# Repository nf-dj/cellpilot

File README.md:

# CellPilot

A controller to pilot UAV/drones via 3G/4G cellular connection.

WARNING: this version of CellPilot will soon be replaced by a new controller using TinyCom instead of Raspberry Pi (http://github.com/nfco/tinycom).

## Pictures

A view of the PCB, a Raspberry Pi "hat":

Inside a 3d-printed prototype box:

CellPilot installed on a DIY drone:

We still rely on an external controller for stabilization.
But a 10DOF sensor module can be installed on the CellPilot board and we can later try to do the stabilization directly on the STM32 processor of the board. (a prototype firmware to do this is already in the repository)

## Video

CellPilot test flight (64Kbps, 10fps):

(the strange colors in the video are due to the PiNoir camera, we will make a new video with a regular Pi camera and some vibration dampening)

## Ordering

A 3d-printed plastic case can be ordered here:
https://www.shapeways.com/shops/netforce

## Contact

Send email to dj@netforce.com.

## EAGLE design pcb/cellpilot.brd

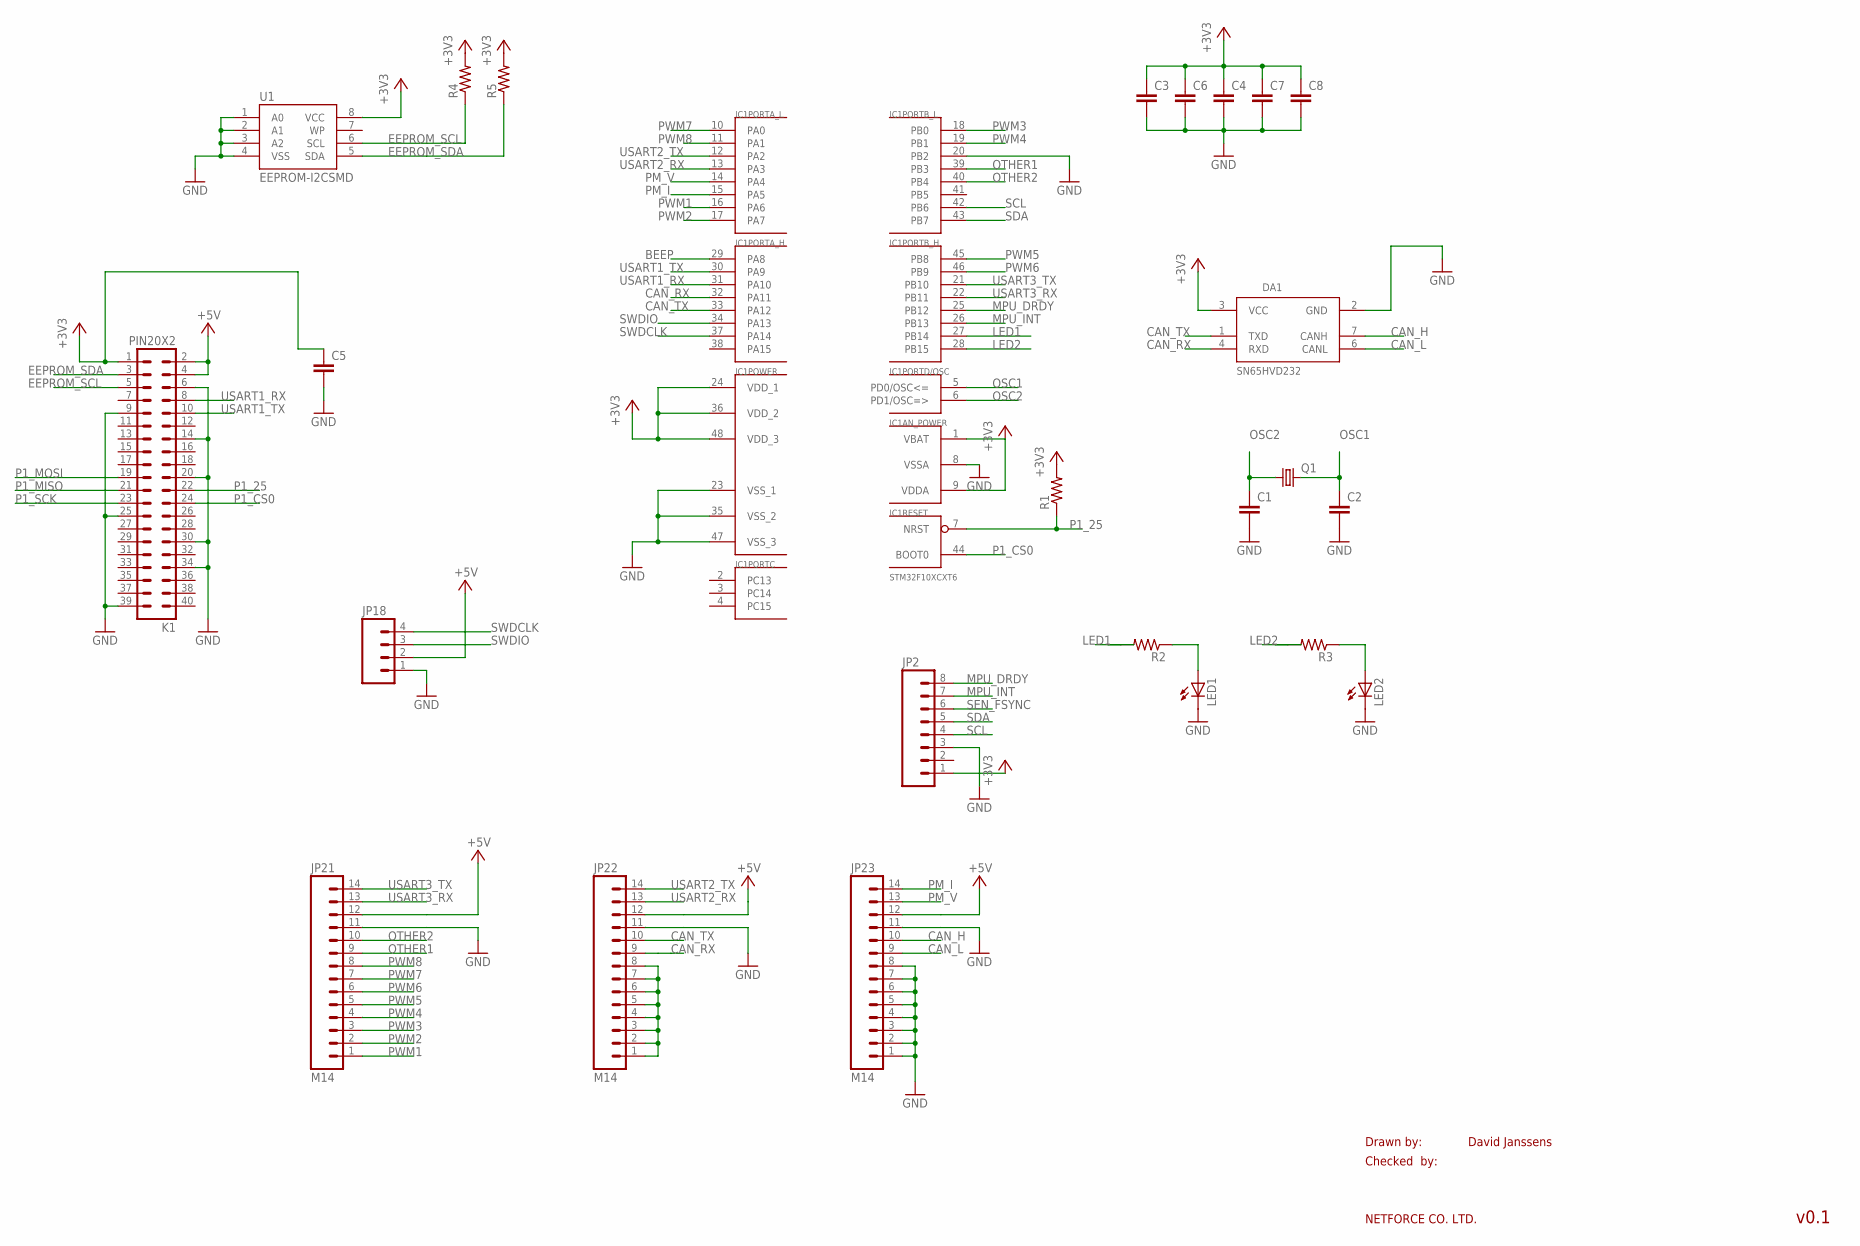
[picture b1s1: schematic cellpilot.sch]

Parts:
C1, C2, C3, C4, C5, C6, C7, C8: CAP0805; 0805
DA1: SN65HVD232; SO08
IC1: STM32F10XCXT6; TQFP48
JP2: M08; 1X08_ROUND
JP18: M04PTH; 1X04
JP21, JP22, JP23: M14; 1X14
K1: PIN20X2; PIN_20X2
LED1, LED2: LED3MM
Q1: CRYSTALHC49S; HC49/S
R1, R2, R3, R4, R5: RESISTOR0805-RES; 0805
U1: EEPROM-I2CSMD; SO08

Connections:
+3V3: C3.1, C4.1, C5.1, C6.1, C7.1, C8.1, DA1.3 (VCC), IC1.1 (VBAT), IC1.9 (VDDA), IC1.24 (VDD_1), IC1.36 (VDD_2), IC1.48 (VDD_3), JP2.1, K1.1, R1.2, R4.2, R5.2, U1.8 (VCC)
+5V: JP18.2, JP21.12, JP22.12, JP23.12, K1.2, K1.4
BEEP: IC1.29 (PA8)
CAN_H: DA1.7 (CANH), JP23.10
CAN_L: DA1.6 (CANL), JP23.9
CAN_RX: DA1.4 (RXD), IC1.32 (PA11), JP22.9
CAN_TX: DA1.1 (TXD), IC1.33 (PA12), JP22.10
EEPROM_SCL: K1.5, R4.1, U1.6 (SCL)
EEPROM_SDA: K1.3, R5.1, U1.5 (SDA)
GND: C1.2, C2.2, C3.2, C4.2, C5.2, C6.2, C7.2, C8.2, DA1.2 (GND), IC1.8 (VSSA), IC1.20 (PB2), IC1.23 (VSS_1), IC1.35 (VSS_2), IC1.47 (VSS_3), JP2.3, JP18.1, JP21.11, JP22.11, JP23.1, JP23.2, JP23.3, JP23.4, JP23.5, JP23.6, JP23.7, JP23.8, JP23.11, K1.6, K1.9, K1.14, K1.20, K1.25, K1.30, K1.34, K1.39, LED1.K (C), LED2.K (C), U1.1 (A0), U1.2 (A1), U1.3 (A2), U1.4 (VSS)
LED1: IC1.27 (PB14), R2.2
LED2: IC1.28 (PB15), R3.2
MPU_DRDY: IC1.25 (PB12), JP2.8
MPU_INT: IC1.26 (PB13), JP2.7
unnamed: LED1.A, R2.1
unnamed: JP22.1, JP22.2, JP22.3, JP22.4, JP22.5, JP22.6, JP22.7, JP22.8
unnamed: LED2.A, R3.1
OSC1: C2.1, IC1.5 (PD0/OSC<=), Q1.2
OSC2: C1.1, IC1.6 (PD1/OSC=>), Q1.1
OTHER1: IC1.39 (PB3), JP21.9
OTHER2: IC1.40 (PB4), JP21.10
P1_25: IC1.7 (NRST), K1.22, R1.1
P1_CS0: IC1.44 (BOOT0), K1.24
P1_MISO: K1.21
P1_MOSI: K1.19
P1_SCK: K1.23
PM_I: IC1.15 (PA5), JP23.14
PM_V: IC1.14 (PA4), JP23.13
PWM1: IC1.16 (PA6), JP21.1
PWM2: IC1.17 (PA7), JP21.2
PWM3: IC1.18 (PB0), JP21.3
PWM4: IC1.19 (PB1), JP21.4
PWM5: IC1.45 (PB8), JP21.5
PWM6: IC1.46 (PB9), JP21.6
PWM7: IC1.10 (PA0), JP21.7
PWM8: IC1.11 (PA1), JP21.8
SCL: IC1.42 (PB6), JP2.4
SDA: IC1.43 (PB7), JP2.5
SEN_FSYNC: JP2.6
SWDCLK: IC1.37 (PA14), JP18.4
SWDIO: IC1.34 (PA13), JP18.3
USART1_RX: IC1.31 (PA10), K1.8
USART1_TX: IC1.30 (PA9), K1.10
USART2_RX: IC1.13 (PA3), JP22.13
USART2_TX: IC1.12 (PA2), JP22.14
USART3_RX: IC1.22 (PB11), JP21.13
USART3_TX: IC1.21 (PB10), JP21.14

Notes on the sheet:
Drawn by:
Checked by:
NETFORCE CO. LTD.
David Janssens
v0.1

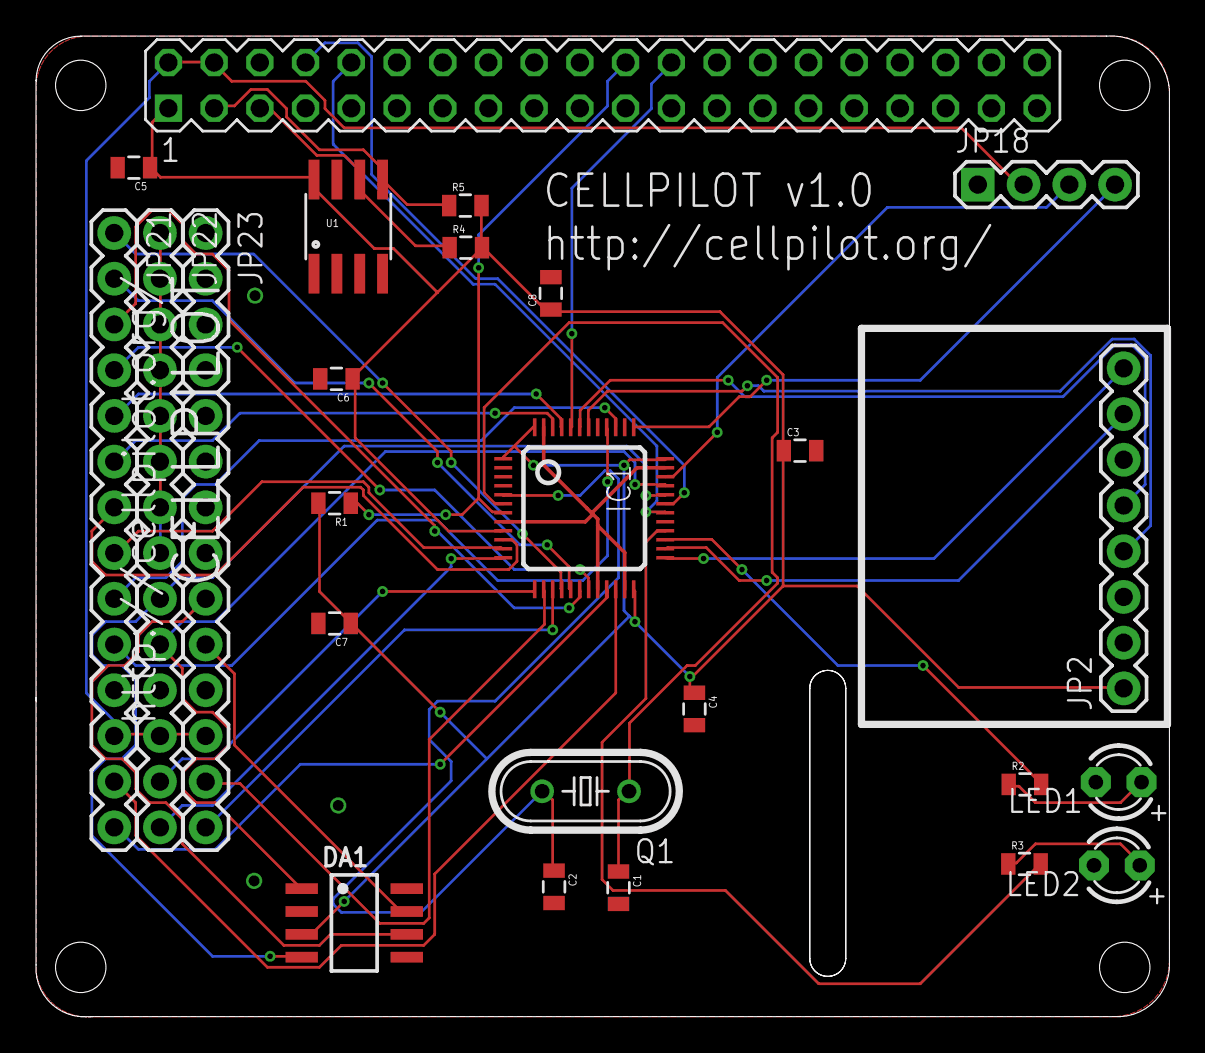
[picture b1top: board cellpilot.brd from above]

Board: 2 copper layers, 63.0 x 54.5 mm, 25 parts (0 on the bottom side), 42 nets.

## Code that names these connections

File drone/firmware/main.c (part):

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    RCC_APB1PeriphClockCmd(RCC_APB1Periph_TIM3 | RCC_APB1Periph_TIM4 | RCC_APB1Periph_TIM2, ENABLE );
}
 
// USART1_TX: PA9
// USART1_RX: PA10
// LED1: PB14
// LED2: PB15
// PWM1: PA6, TIM3_CH1
// PWM2: PA7, TIM3_CH2
// PWM3: PB0, TIM3_CH3
// PWM4: PB1, TIM3_CH4
// PWM5: PB8, TIM4_CH3
// PWM6: PB9, TIM4_CH4
// PWM7: PA0, TIM2_CH1
// PWM8: PA1, TIM2_CH2

void init_gpio() {
    GPIO_InitTypeDef gpio_init_struct;
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
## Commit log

2015-09-24 first
2015-09-24 case
2015-09-24 fix controls
2015-09-24 add stm32loader
2015-09-26 controls
2015-09-30 license
2015-09-30 readme
2015-09-30 add .gitignore
2015-10-01 old AVR firmware
2015-10-03 add yaw control on gamepad
2015-10-04 add case file
2015-10-04 image
2015-10-04 update pcb
2015-10-05 rename to cellpilot, because found different project named raspilot...
2015-10-05 move connector
2015-10-06 update case
2015-10-10 impove case
2015-10-12 video
2015-10-12 broken igg link
2015-10-13 fix img
2015-11-20 remove IGG link

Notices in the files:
drone/firmware/main.c:
Copyright (c) 2015 Netforce Co. Ltd.
parts and their libraries:
SparkFun-Connectors: Licensing: Creative Commons ShareAlike 4.0 International - https://creativecommons.org/licenses/by-sa/4.0
